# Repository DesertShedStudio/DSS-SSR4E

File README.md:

DSS-SSR4E
============

The "DSS-SSR4E" is a OSHWA Certified hardware design, providing four isolated SSR outputs and a single isolated
ABZ encoder input. Compatible with Mesa Ethernet Anything I/O Cards and Mesa Electronics HostMot2 configurations.

DSS-SSR4E <br>
"Desert Shed Stuido SSR x4 + Encoder"

This repository is aimed towards those who wish to manufacture their own boards. 

Media
=======

| KICAD RENDER           | HAND SOLDERED PROTOTYPE  |
| ---------------------- | ------------------------ |
| |  |

| BENCHTEST VIDEO |
| --------------- |
|  |

Contribute 
===========
I am #notsponsored ! Your direct support by using my affiliate links / shopping with affiliate retailers goes a long way
in helping me to produce more open source hardware. Thank You. 

Amazon: https://amzn.to/3v1R42O <br>
Openbuilds:  https://openbuildspartstore.com/?ref=hGMJTVfeW_r4W

License
=======

DSS-SSR4E | https://github.com/DesertShedStudio/DSS-SSR4E <br>
Copyright (c) Desert Shed Studio

This source describes Open Hardware and is licensed under the CERN-OHL-S v2.

You may redistribute and modify this source and make products using it under <br>
the terms of the CERN-OHL-S v2 (https://ohwr.org/cern_ohl_s_v2.txt). <br>

This source is distributed WITHOUT ANY EXPRESS OR IMPLIED WARRANTY, <br>
INCLUDING OF MERCHANTABILITY, SATISFACTORY QUALITY AND FITNESS FOR A <br>
PARTICULAR PURPOSE. Please see the CERN-OHL-S v2 for applicable conditions.

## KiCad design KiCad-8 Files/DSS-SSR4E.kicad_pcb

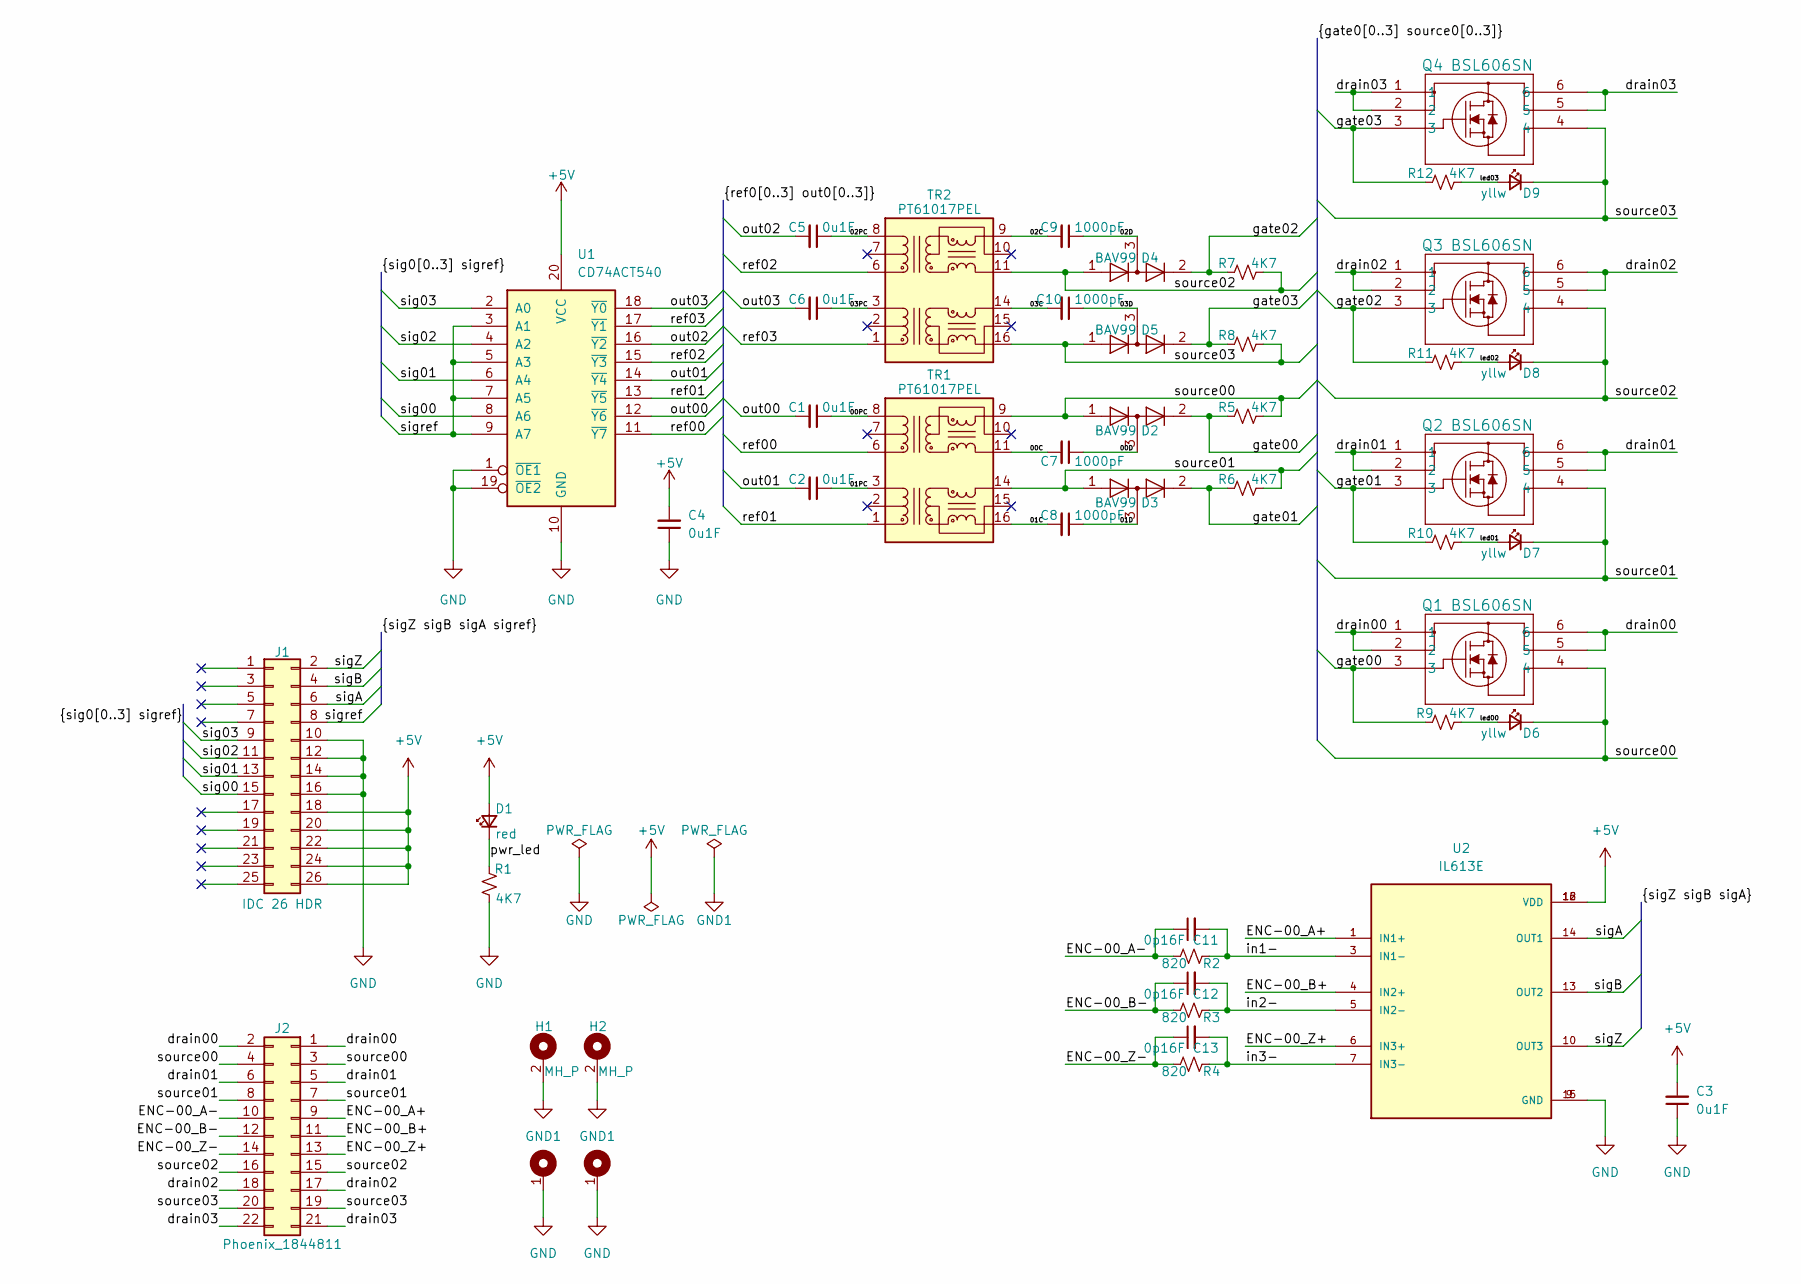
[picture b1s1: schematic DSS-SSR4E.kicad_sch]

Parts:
C1, C2, C3, C4, C5, C6: 0u1F; C_0603_1608Metric
C7, C8, C9, C10: 1000pF; C_0603_1608Metric
C11, C12, C13: 0p16F; C_0603_1608Metric
D1: red; LED_0603_simple_silk
D2, D3, D4, D5: BAV99; SOT-23
D6, D7, D8, D9: yllw; LED_0603_simple_silk
H1, H2: MH_P; Phoenix Contact 1201578 Pinout 1-2
J1: IDC 26 HDR; IDC 26 HDR 2.54
J2: Phoenix_1844811; Phoenix Contact 1844811
Q1, Q2, Q3, Q4: BSL606SN; TSOP-6_1.65x3.05mm_P0.95mm
R1, R5, R6, R7, R8, R9, R10, R11, R12: 4K7; R_0603_1608Metric
R2, R3, R4: 820; R_0603_1608Metric
TR1, TR2: PT61017PEL; Transformer_Ethernet_Bourns_PT61017PEL
U1: CD74ACT540; TSSOP-20_4.4x6.5mm_P0.65mm
U2: IL613E; NVE_IL613E; PARTREV AC

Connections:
+5V: C3.2, C4.2, D1.2 (A), J1.18, J1.20, J1.22, J1.24, J1.26, U1.20 (VCC), U2.12 (VDD), U2.16 (VDD)
/00C: C7.2, TR1.11 (RX+)
/00D: C7.1, D2.3 (K)
/00PC: C1.1, TR1.8 (RD-)
/01C: C8.2, TR1.16 (TX+)
/01D: C8.1, D3.3 (K)
/01PC: C2.1, TR1.3 (TD-)
/02C: C9.2, TR2.9 (RX-)
/02D: C9.1, D4.3 (K)
/02PC: C5.1, TR2.8 (RD-)
/03C: C10.2, TR2.14 (TX-)
/03D: C10.1, D5.3 (K)
/03PC: C6.1, TR2.3 (TD-)
/ENC-00_A+: J2.9, U2.1 (IN1+)
/ENC-00_A-: C11.1, J2.10, R2.2
/ENC-00_B+: J2.11, U2.4 (IN2+)
/ENC-00_B-: C12.1, J2.12, R3.2
/ENC-00_Z+: J2.13, U2.6 (IN3+)
/ENC-00_Z-: C13.1, J2.14, R4.2
/drain00: J2.1, J2.2, Q1.1, Q1.2, Q1.5, Q1.6
/drain01: J2.5, J2.6, Q2.1, Q2.2, Q2.5, Q2.6
/drain02: J2.17, J2.18, Q3.1, Q3.2, Q3.5, Q3.6
/drain03: J2.21, J2.22, Q4.1, Q4.2, Q4.5, Q4.6
/gate00: D2.2 (A), Q1.3, R5.1, R9.1
/gate01: D3.2 (A), Q2.3, R6.1, R10.1
/gate02: D4.2 (A), Q3.3, R7.1, R11.1
/gate03: D5.2 (A), Q4.3, R8.1, R12.1
/in1-: C11.2, R2.1, U2.3 (IN1-)
/in2-: C12.2, R3.1, U2.5 (IN2-)
/in3-: C13.2, R4.1, U2.7 (IN3-)
/led00: D6.2 (A), R9.2
/led01: D7.2 (A), R10.2
/led02: D8.2 (A), R11.2
/led03: D9.2 (A), R12.2
/out00: C1.2, U1.12 (~Y6)
/out01: C2.2, U1.14 (~Y4)
/out02: C5.2, U1.16 (~Y2)
/out03: C6.2, U1.18 (~Y0)
/pwr_led: D1.1 (K), R1.1
/ref00: TR1.6 (RD+), U1.11 (~Y7)
/ref01: TR1.1 (TD+), U1.13 (~Y5)
/ref02: TR2.6 (RD+), U1.15 (~Y3)
/ref03: TR2.1 (TD+), U1.17 (~Y1)
/sig00: J1.15, U1.8 (A6)
/sig01: J1.13, U1.6 (A4)
/sig02: J1.11, U1.4 (A2)
/sig03: J1.9, U1.2 (A0)
/sigA: J1.6, U2.14 (OUT1)
/sigB: J1.4, U2.13 (OUT2)
/sigZ: J1.2, U2.10 (OUT3)
/sigref: J1.8, U1.3 (A1), U1.5 (A3), U1.7 (A5), U1.9 (A7)
/source00: D2.1 (K), D6.1 (K), J2.3, J2.4, Q1.4, R5.2, TR1.9 (RX-)
/source01: D3.1 (K), D7.1 (K), J2.7, J2.8, Q2.4, R6.2, TR1.14 (TX-)
/source02: D4.1 (K), D8.1 (K), J2.15, J2.16, Q3.4, R7.2, TR2.11 (RX+)
/source03: D5.1 (K), D9.1 (K), J2.19, J2.20, Q4.4, R8.2, TR2.16 (TX+)
GND: C3.1, C4.1, H1.1, H2.1, J1.10, J1.12, J1.14, J1.16, R1.2, U1.1 (~OE1), U1.10 (GND), U1.19 (~OE2), U2.9 (GND), U2.15 (GND)
GND1: H1.2, H2.2

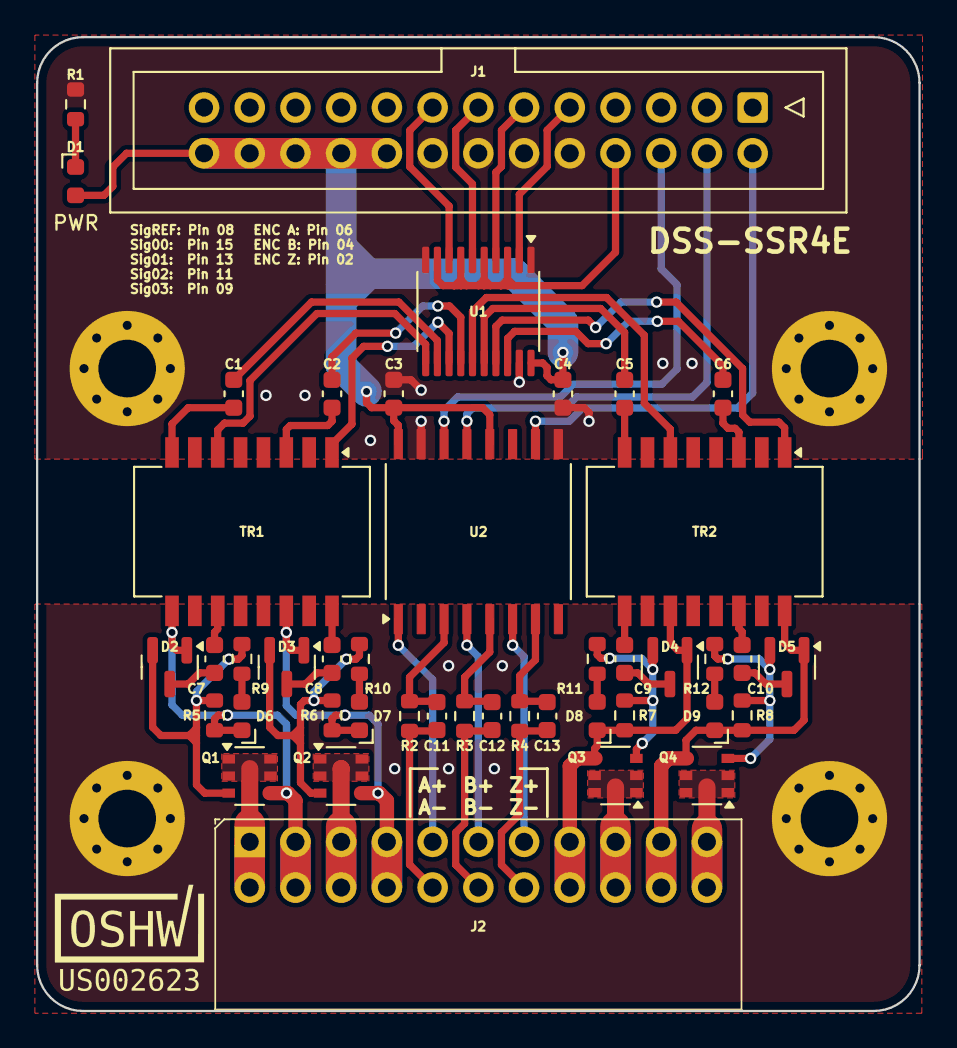
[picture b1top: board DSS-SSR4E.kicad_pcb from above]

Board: 2 copper layers, 49.0 x 54.1 mm, 46 parts (0 on the bottom side), 57 nets.

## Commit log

2024-04-09 Add files via upload
    Initial file upload.
2024-04-10 Add files via upload
    add files required to enable youtube embedding.
2024-04-10 Update README.md
    testing youtube embed.
2024-04-10 Delete _includes directory
    embedding youtube video was a fail.
2024-04-10 Update README.md
    Fixed YouTube video embed.
2024-04-24 update gerber files for OSHWA cert.
2024-04-24 update kicad render for OSHWA cert.
2024-04-24 update kicad files for OSHWA cert.
